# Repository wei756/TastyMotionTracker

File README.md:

# TastyMotionTracker
TastyMotionTracker-SlimeVR PCB SMT Project

- Very tiny size
- Using BMI160 6-DoF IMU
- I2C port for additional IMU
- CH340E UART-USB Interface
- Charging Li-Po Battery support

## License
**This hardware is licensed under the CERN-OHL-P v2 license**, which is a permissive,
non-viral and non-reciprocal open hardware license. Unlike software licenses like
MIT and Apache 2.0, it better handles the nuances of hardware and protects both
the licensor and licensee from patent lawsuits.

**Unless you explicitly state otherwise, any contribution intentionally submitted
for inclusion in this work by you, shall be licensed as above, without any
additional terms or conditions.**

### Conveying notice of License
Note that as part of the CERN-OHL-P v2 license, recipients of manufactured
hardware must also receive notice of the above license. One such
method of conveying the notice is to include a link to the original source repo,
or printing "Licensed under CERN-OHL-P v2" on the PCB silkscreen. For more info,
see [here](https://ohwr.org/project/cernohl/wikis/Documents/CERN-OHL-version-2).

This is conceptually similar to the MIT/Apache 2.0 Licenses, where the original
license must still be included as a notice even when the source is modified and
subsequently relicensed under different terms.

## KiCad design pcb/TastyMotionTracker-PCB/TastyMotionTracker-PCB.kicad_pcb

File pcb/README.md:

# TastyMotionTracker-PCB

### TODO
- fix battery indicator.

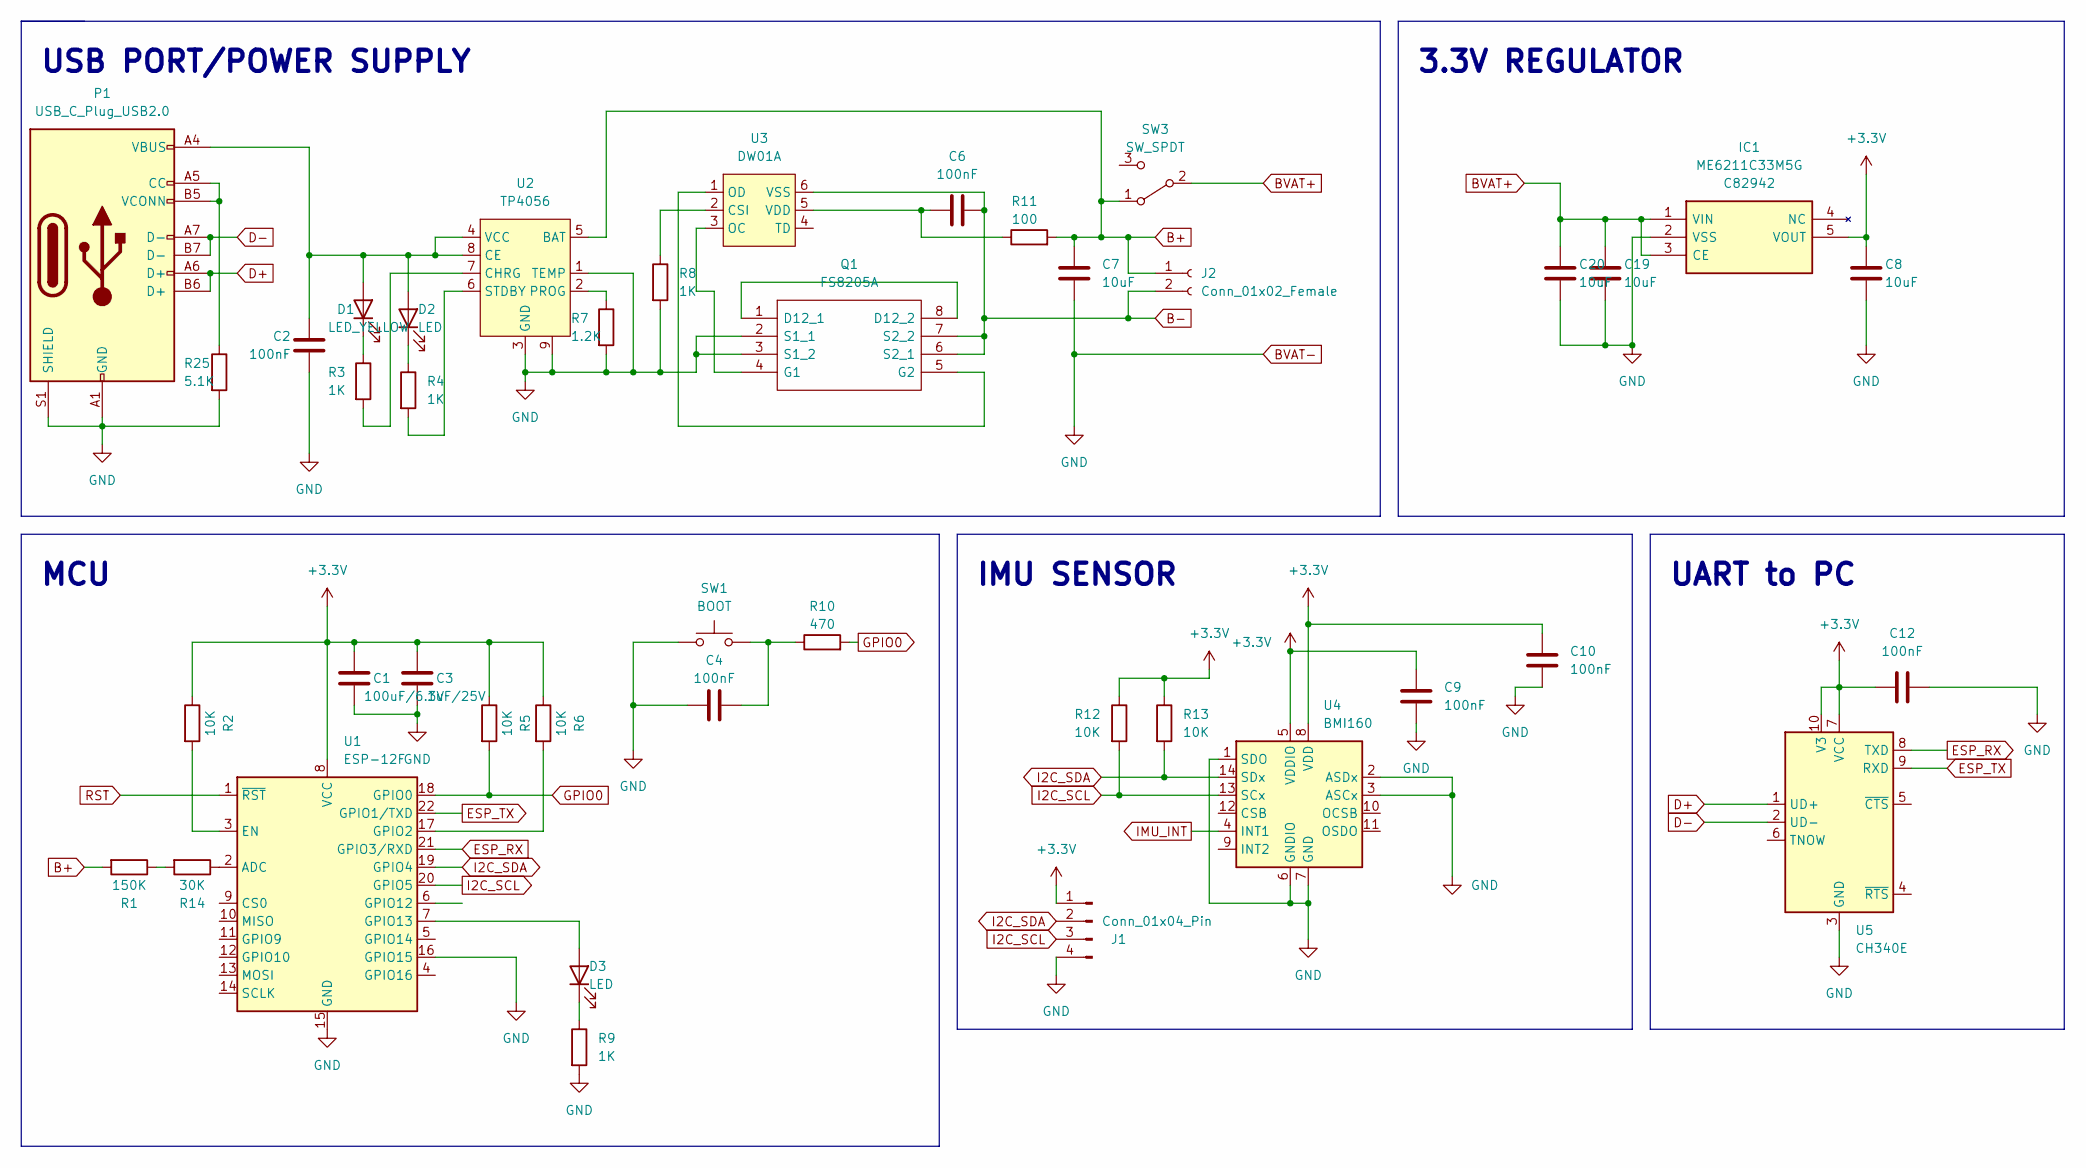
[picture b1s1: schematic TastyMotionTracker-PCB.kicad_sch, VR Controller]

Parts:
C1: 100uF/6.3V; C_1206_3216Metric; LCSC C15008
C2, C4, C6, C9, C10, C12: 100nF; C_0402_1005Metric; LCSC C1525
C3: 1uF/25V; C_0402_1005Metric; LCSC C52923
C7, C8, C19, C20: 10uF; C_0402_1005Metric; LCSC C15525
D1: LED_YELLOW; LED_0603_1608Metric; LCSC C72038
D2, D3: LED; LED_0603_1608Metric; LCSC C72041
IC1: ME6211C33M5G; SOT95P282X145-5N; Manufacturer_Part_Number ME6211C33M5G; LCSC C82942
J1: Conn_01x04_Pin; JST_PH_S4B-PH-K_1x04_P2.00mm_Horizontal; LCSC C157926
J2: Conn_01x02_Female; Molex_PicoBlade_53261-0271_1x02-1MP_P1.25mm_Horizontal; LCSC C189700
P1: USB_C_Plug_USB2.0; USB_C_Receptacle_HRO_TYPE-C-31-M-12; LCSC C167321
Q1: FS8205A; SOP65P640X120-8N; Manufacturer_Part_Number FS8205A; LCSC C16052
R1: 150K; R_0603_1608Metric; LCSC C22807
R2, R5, R6, R12, R13: 10K; R_0402_1005Metric; LCSC C25744
R3, R4, R8, R9: 1K; R_0402_1005Metric; LCSC C11702
R7: 1.2K; R_0603_1608Metric; LCSC C22765
R10: 470; R_0402_1005Metric; LCSC C25117
R11: 100; R_0402_1005Metric; LCSC C25076
R14: 30K; R_0603_1608Metric; LCSC C22984
R25: 5.1K; R_0402_1005Metric; LCSC C25905
SW1: BOOT; SW_SPST_SKQG_WithoutStem; LCSC C318884
SW3: SW_SPDT; SW_SPDT_PCM12; LCSC C319019
U1: ESP-12F; ESP-12E; LCSC C82891
U2: TP4056; HSOP-8-1EP_3.9x4.9mm_P1.27mm_EP2.41x3.1mm; LCSC C16581
U3: DW01A; SOT-23-6; LCSC C61503
U4: BMI160; Bosch_LGA-14_3x2.5mm_P0.5mm; LCSC C94021
U5: CH340E; MSOP-10_3x3mm_P0.5mm; LCSC C99652

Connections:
+3V3: C1.1, C3.1, C8.1, C9.1, C10.1, C12.1, IC1.5 (VOUT), J1.1, R2.1, R5.1, R6.1, R12.1, R13.1, U1.8 (VCC), U4.5 (VDDIO), U4.8 (VDD), U5.7 (VCC), U5.10 (V3)
B+: C7.1, J2.1, R1.2, R11.2, SW3.1 (A), U2.5 (BAT)
B-: C6.2, J2.2, Q1.6 (S2_1), Q1.7 (S2_2), U3.6 (VSS)
BVAT+: C19.1, C20.1, IC1.1 (VIN), IC1.3 (CE), SW3.2 (B)
BVAT-: C1.2, C2.2, C3.2, C4.1, C7.2, C8.2, C9.2, C10.2, C12.2, C19.2, C20.2, IC1.2 (VSS), J1.4, P1.A1 (GND), P1.A12 (GND), P1.B1 (GND), P1.B12 (GND), P1.S1 (SHIELD), Q1.2 (S1_1), Q1.3 (S1_2), R7.2, R8.2, R9.2, R25.2, SW1.1, U1.15 (GND), U1.16 (GPIO15), U2.1 (TEMP), U2.3 (GND), U2.9, U4.1 (SDO), U4.2 (ASDx), U4.3 (ASCx), U4.6 (GNDIO), U4.7 (GND), U5.3 (GND)
D+: P1.A6 (D+), P1.B6 (D+), U5.1 (UD+)
D-: P1.A7 (D-), P1.B7 (D-), U5.2 (UD-)
ESP_RX: U1.21 (GPIO3/RXD), U5.8 (TXD)
ESP_TX: U1.22 (GPIO1/TXD), U5.9 (RXD)
GPIO0: R5.2, R10.2, U1.18 (GPIO0)
I2C_SCL: J1.3, R12.2, U1.20 (GPIO5), U4.13 (SCx)
I2C_SDA: J1.2, R13.2, U1.19 (GPIO4), U4.14 (SDx)
IMU_INT: U4.4 (INT1)
unnamed: C4.2, R10.1, SW1.2
unnamed: C2.1, D1.2 (A), D2.2 (A), P1.A4 (VBUS), P1.A9 (VBUS), P1.B4 (VBUS), P1.B9 (VBUS), U2.4 (VCC), U2.8 (CE)
unnamed: D1.1 (K), R3.1
unnamed: D2.1 (K), R4.1
unnamed: D3.2 (A), U1.7 (GPIO13)
unnamed: D3.1 (K), R9.1
unnamed: P1.A5 (CC), P1.B5 (VCONN), R25.1
unnamed: Q1.1 (D12_1), Q1.8 (D12_2)
unnamed: Q1.4 (G1), U3.3 (OC)
unnamed: Q1.5 (G2), U3.1 (OD)
unnamed: R1.1, R14.2
unnamed: R14.1, U1.2 (ADC)
unnamed: R2.2, U1.3 (EN)
unnamed: R6.2, U1.17 (GPIO2)
unnamed: R3.2, U2.7 (CHRG)
unnamed: R7.1, U2.2 (PROG)
unnamed: R4.2, U2.6 (STDBY)
unnamed: R8.1, U3.2 (CSI)
unnamed: C6.1, R11.1, U3.5 (VDD)
RST: U1.1 (~RST)

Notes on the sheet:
USB PORT/POWER SUPPLY
MCU
IMU SENSOR
3.3V REGULATOR
UART to PC

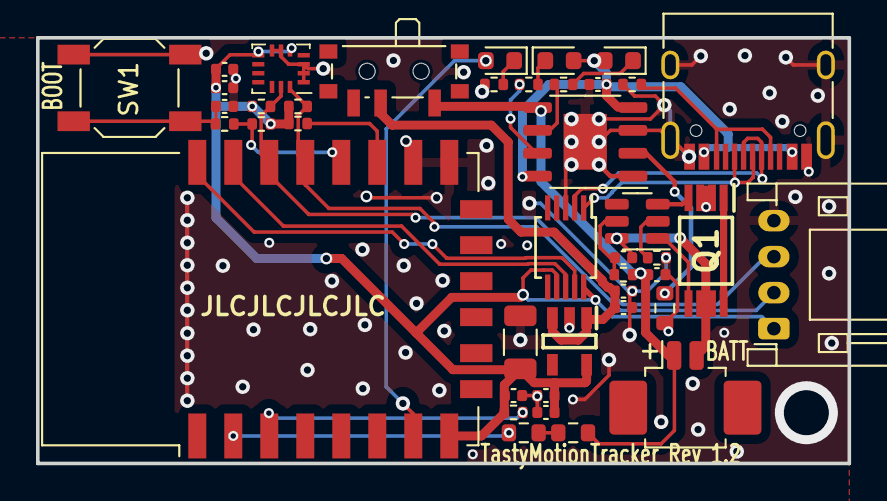
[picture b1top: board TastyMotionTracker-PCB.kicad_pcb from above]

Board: 2 copper layers, 45.1 x 23.6 mm, 42 parts (0 on the bottom side), 31 nets.

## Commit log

2024-02-22 Upload LICENSE
2024-03-07 upload images
2024-03-08 upload pcb project
2024-03-08 upload 3d printing models
